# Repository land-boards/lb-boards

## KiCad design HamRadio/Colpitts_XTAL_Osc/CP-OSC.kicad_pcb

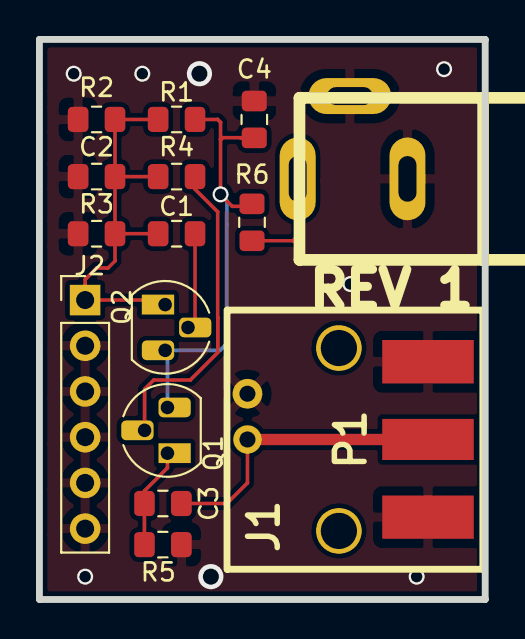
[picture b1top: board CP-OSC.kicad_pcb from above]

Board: 2 copper layers, 24.8 x 31.1 mm, 16 parts (0 on the bottom side), 8 nets.

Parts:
C1, C2: 470PF; C_0805_2012Metric_Pad1.15x1.40mm_HandSolder
C3: 100pF; C_0805_2012Metric_Pad1.15x1.40mm_HandSolder
C4: 0.1uF; C_0805_2012Metric_Pad1.15x1.40mm_HandSolder
J1: BNC; BNC-RT
J2: Conn_01x06; PinHeader_1x06_P2.54mm_Vertical
J3: DCJ0202; DCJ-NEW-Slotted
P1: SMA; SMA_EDGE
Q1, Q2: 2N3904; TO-92_HandSolder
R1, R2: 10K; R_0805_2012Metric_Pad1.15x1.40mm_HandSolder
R3, R4, R5: 1K; R_0805_2012Metric_Pad1.15x1.40mm_HandSolder
R6: 47; R_0805_2012Metric_Pad1.15x1.40mm_HandSolder

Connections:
GND: C2.2, C4.2, J1.2, J2.2, J2.3, J2.4, J2.5, J2.6, J3.2, J3.3, P1.2, R2.1, R3.1, R5.1
unnamed: C1.1, Q1.2
unnamed: C1.2, C2.1, J2.1, Q1.1, R1.1, R2.2, R3.2, R4.2
unnamed: C3.1, J1.1, P1.1
unnamed: C3.2, Q2.1, R5.2
unnamed: C4.1, Q1.3, Q2.3, R1.2, R6.2
unnamed: J3.1, R6.1
unnamed: Q2.2, R4.1

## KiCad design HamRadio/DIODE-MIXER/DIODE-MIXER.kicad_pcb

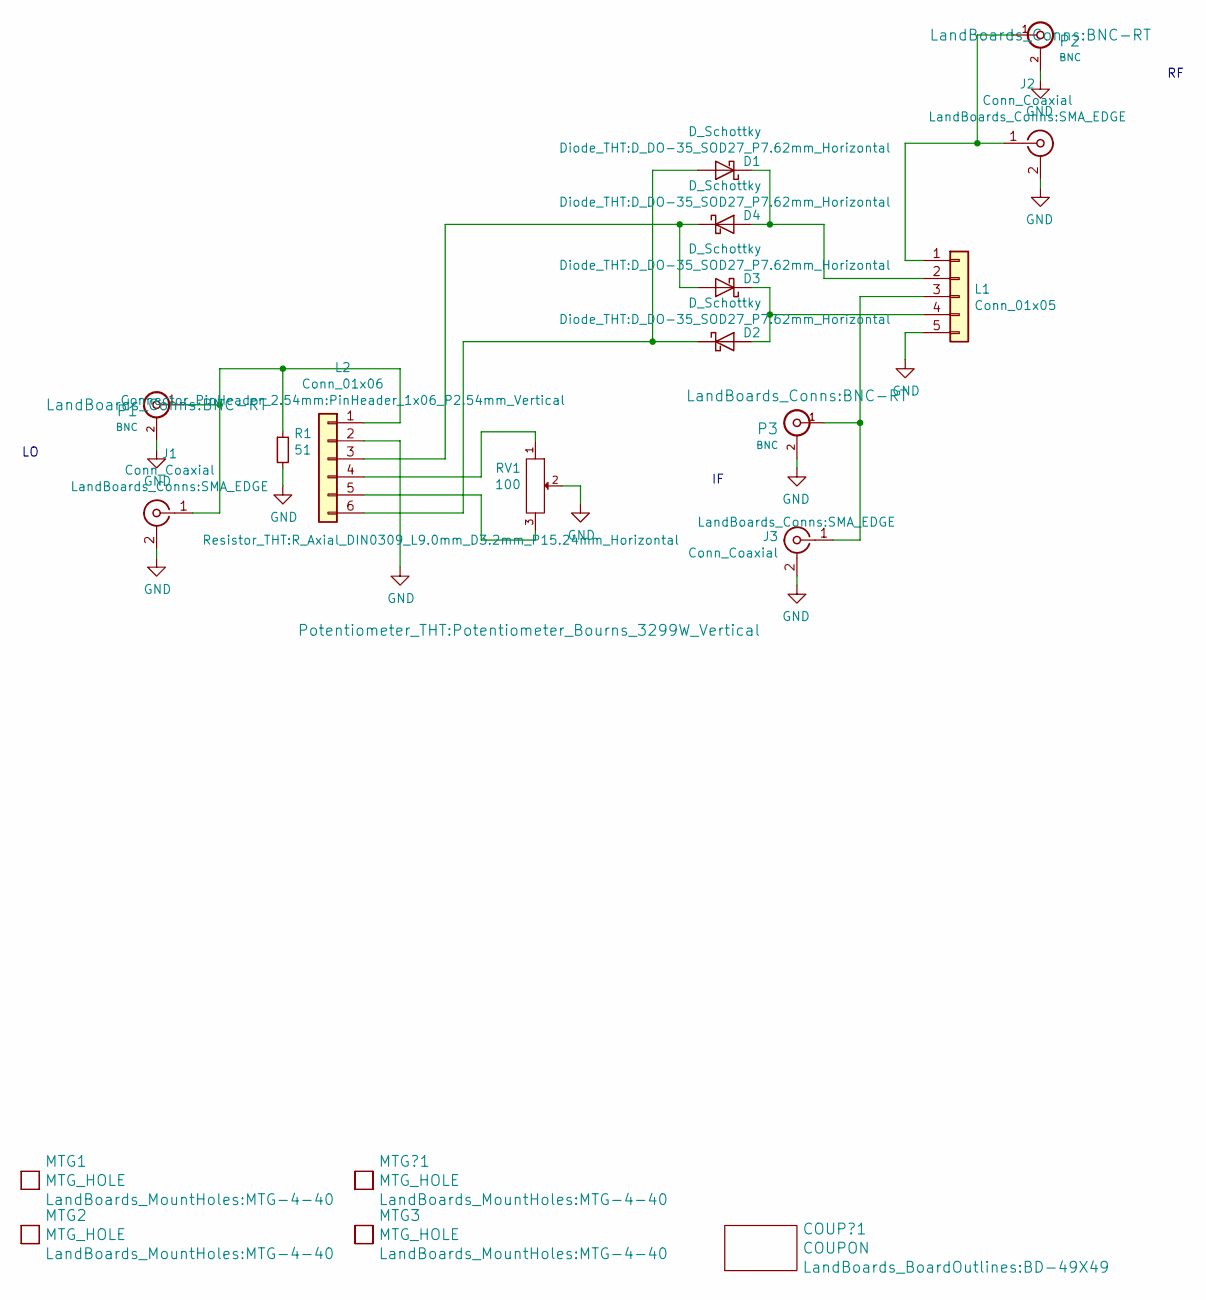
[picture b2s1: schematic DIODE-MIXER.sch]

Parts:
COUP?1: COUPON; BD-49X49
D1, D2, D3, D4: D_Schottky; D_DO-35_SOD27_P7.62mm_Horizontal
J1, J2, J3: Conn_Coaxial; SMA_EDGE
L1: Conn_01x05; PinHeader_1x05_P2.54mm_Vertical
L2: Conn_01x06; PinHeader_1x06_P2.54mm_Vertical
MTG1, MTG2, MTG3: MTG_HOLE; MTG-4-40
MTG?1: MTG_HOLE; MTG-4-40
P1, P2, P3: BNC; BNC-RT
R1: 51; R_Axial_DIN0309_L9.0mm_D3.2mm_P15.24mm_Horizontal
RV1: 100; Potentiometer_Bourns_3299W_Vertical

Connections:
GND: J1.2 (Ext), J2.2 (Ext), J3.2 (Ext), L1.5, L2.2, P1.2 (Ext), P2.2 (Ext), P3.2 (Ext), R1.2, RV1.2
unnamed: D1.1 (K), D4.2 (A), L1.2
unnamed: D1.2 (A), D2.1 (K), L2.6
unnamed: D2.2 (A), D3.1 (K), L1.4
unnamed: D3.2 (A), D4.1 (K), L2.3
unnamed: J1.1 (In), L2.1, P1.1 (In), R1.1
unnamed: J2.1 (In), L1.1, P2.1 (In)
unnamed: J3.1 (In), L1.3, P3.1 (In)
unnamed: L2.4, RV1.1
unnamed: L2.5, RV1.3

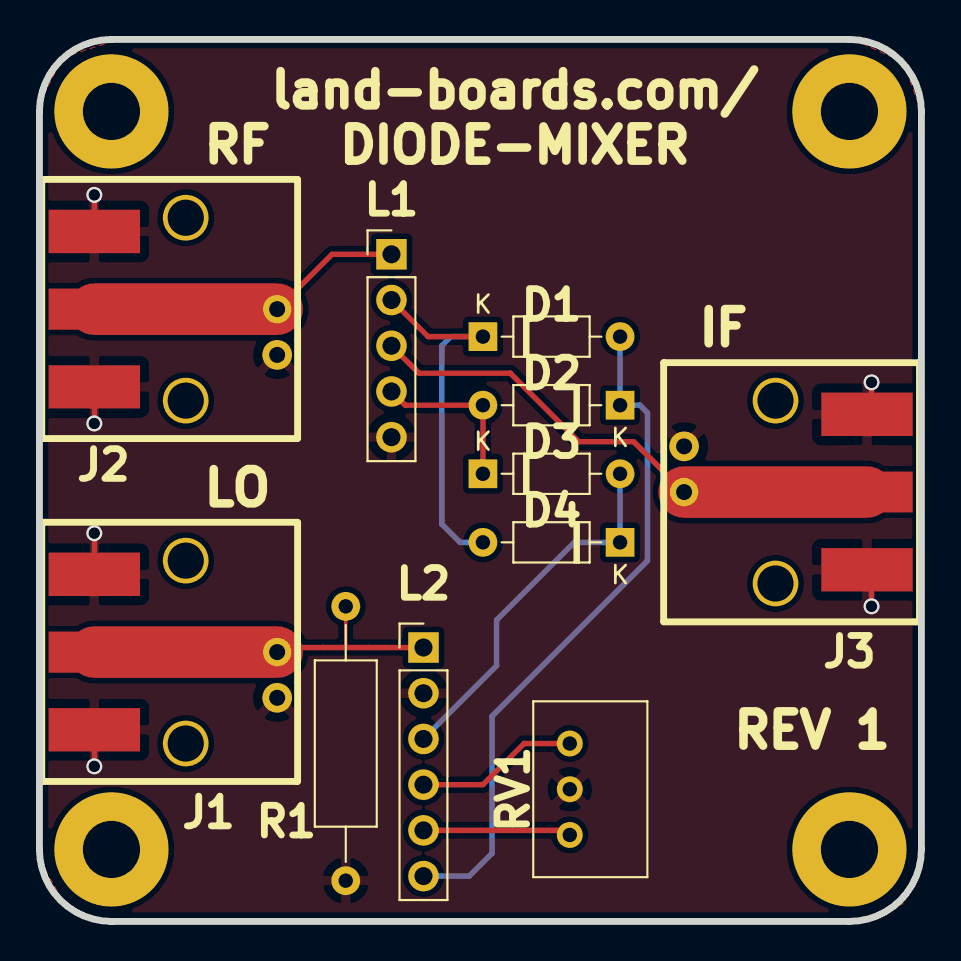
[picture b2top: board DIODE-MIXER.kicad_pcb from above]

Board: 2 copper layers, 49.0 x 49.0 mm, 18 parts (0 on the bottom side), 10 nets.

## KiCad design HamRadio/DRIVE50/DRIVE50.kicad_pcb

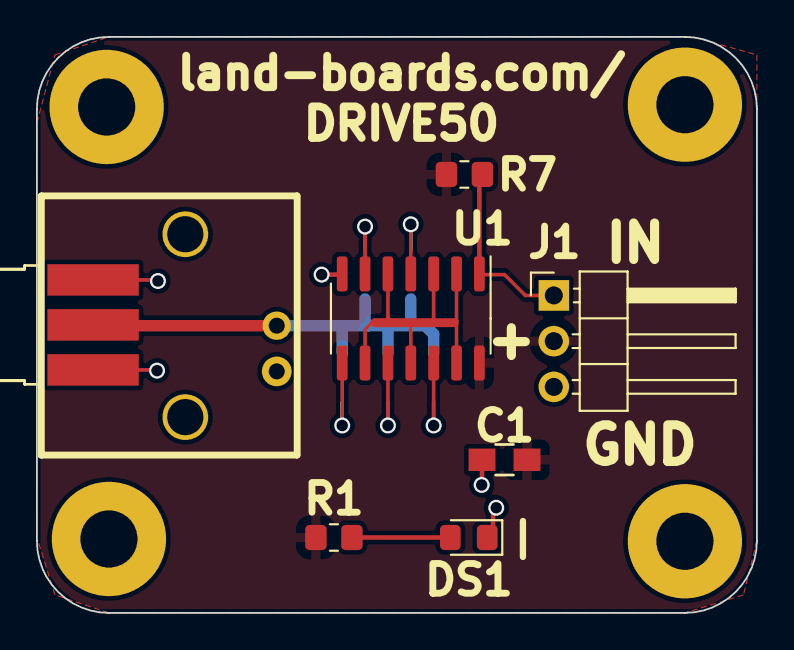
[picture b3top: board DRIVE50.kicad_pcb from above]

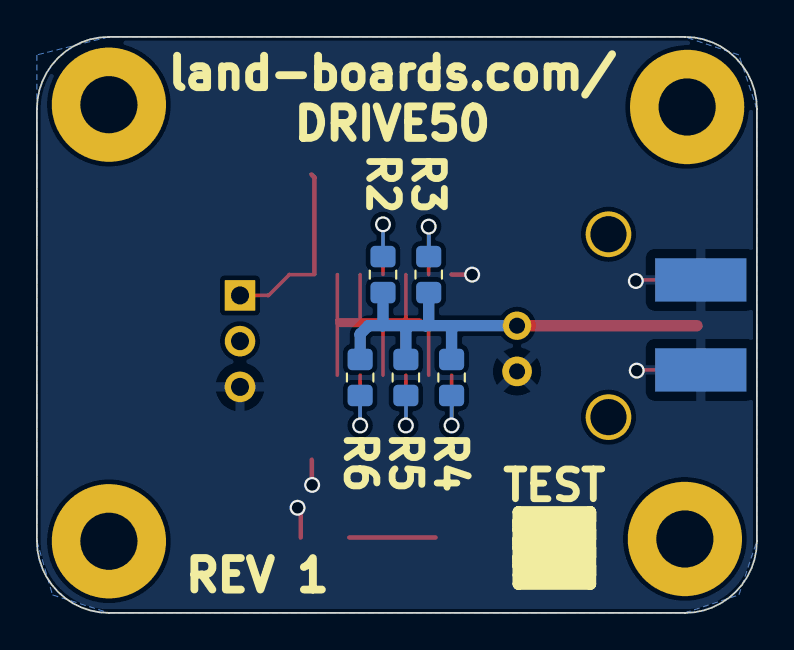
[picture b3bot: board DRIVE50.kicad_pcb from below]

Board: 2 copper layers, 40.0 x 32.0 mm, 18 parts (5 on the bottom side), 11 nets.

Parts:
C1: 0.1uF; C_0805_HandSoldering
DS1: LED; LED_0805_2012Metric_Pad1.15x1.40mm_HandSolder
J1: Conn_01x03; PinHeader_1x03_P2.54mm_Horizontal
MTG1, MTG2, MTG3, MTG4: MTG_HOLE; MTG-4-40
PA1: SMA; SMA_EDGE-F
PB1: BNC; BNC-RT
R1: 240; R_0805_2012Metric_Pad1.20x1.40mm_HandSolder
R2, R3, R4, R5, R6: 249; R_0805_2012Metric_Pad1.20x1.40mm_HandSolder
R7: 10K; R_0805_2012Metric_Pad1.20x1.40mm_HandSolder
TEST: COUPON; TEST_BLK-REAR
U1: 74AC14; SO-14_3.9x8.65mm_P1.27mm

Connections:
GND: C1.2, DS1.1 (K), J1.3, PA1.2 (Ext), PB1.2 (Ext), U1.7 (GND)
unnamed: DS1.2 (A), R1.2
unnamed: J1.1, R7.1, U1.1
unnamed: PA1.1 (In), PB1.1 (In), R2.2, R3.2, R4.2, R5.2, R6.2
unnamed: R2.1, U1.4
unnamed: R3.1, U1.6
unnamed: R4.1, U1.8
unnamed: R5.1, U1.10
unnamed: R6.1, U1.12
unnamed: U1.2, U1.3, U1.5, U1.9, U1.11, U1.13
VCC: C1.1, J1.2, R1.1, R7.2, U1.14 (VCC)

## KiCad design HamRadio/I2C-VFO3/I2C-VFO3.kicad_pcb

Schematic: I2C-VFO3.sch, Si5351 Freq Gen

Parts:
C1, C2: 0.1uF; C_0805_2012Metric_Pad1.15x1.40mm_HandSolder
J1: Conn_02x04_Odd_Even; PinHeader_2x04_P2.54mm_Vertical
J2: Conn_02x03_Odd_Even; PinHeader_2x03_P2.54mm_Vertical
R1, R2: 2.2K; R_0805_2012Metric_Pad1.15x1.40mm_HandSolder
U1: Si5351A; MSOP-10_3x3mm_P0.5mm
U2: ASE-xxxMHz; Oscillator_SMD_EuroQuartz_XO53-4Pin_5.0x3.2mm_HandSoldering

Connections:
+3V3: C1.1, J1.5, J1.6, R1.1, R2.1, U1.1 (VCC), U1.7 (VCCO), U2.4
/SCL: J1.1, J1.2, R1.2, U1.4 (SCL)
/SDA: J1.3, J1.4, R2.2, U1.5 (SDA)
GND: C1.2, J1.7, J1.8, J2.2, J2.4, J2.6, U1.8 (GND), U2.2
unnamed: C2.1, U1.2 (XA)
unnamed: C2.2, U2.3
unnamed: J2.1, U1.10 (CLK0)
unnamed: J2.3, U1.9 (CLK1)
unnamed: J2.5, U1.6 (CLK2)

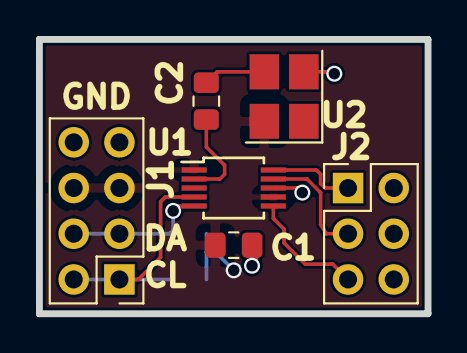
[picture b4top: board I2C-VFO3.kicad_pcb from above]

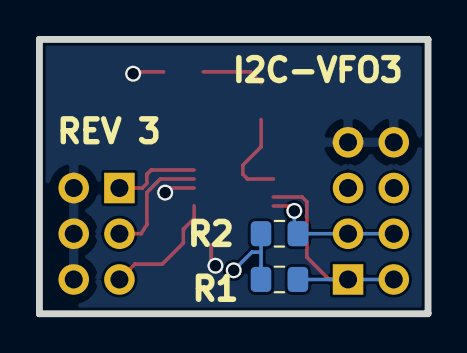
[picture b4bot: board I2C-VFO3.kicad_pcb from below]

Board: 2 copper layers, 21.6 x 15.2 mm, 8 parts (2 on the bottom side), 9 nets.

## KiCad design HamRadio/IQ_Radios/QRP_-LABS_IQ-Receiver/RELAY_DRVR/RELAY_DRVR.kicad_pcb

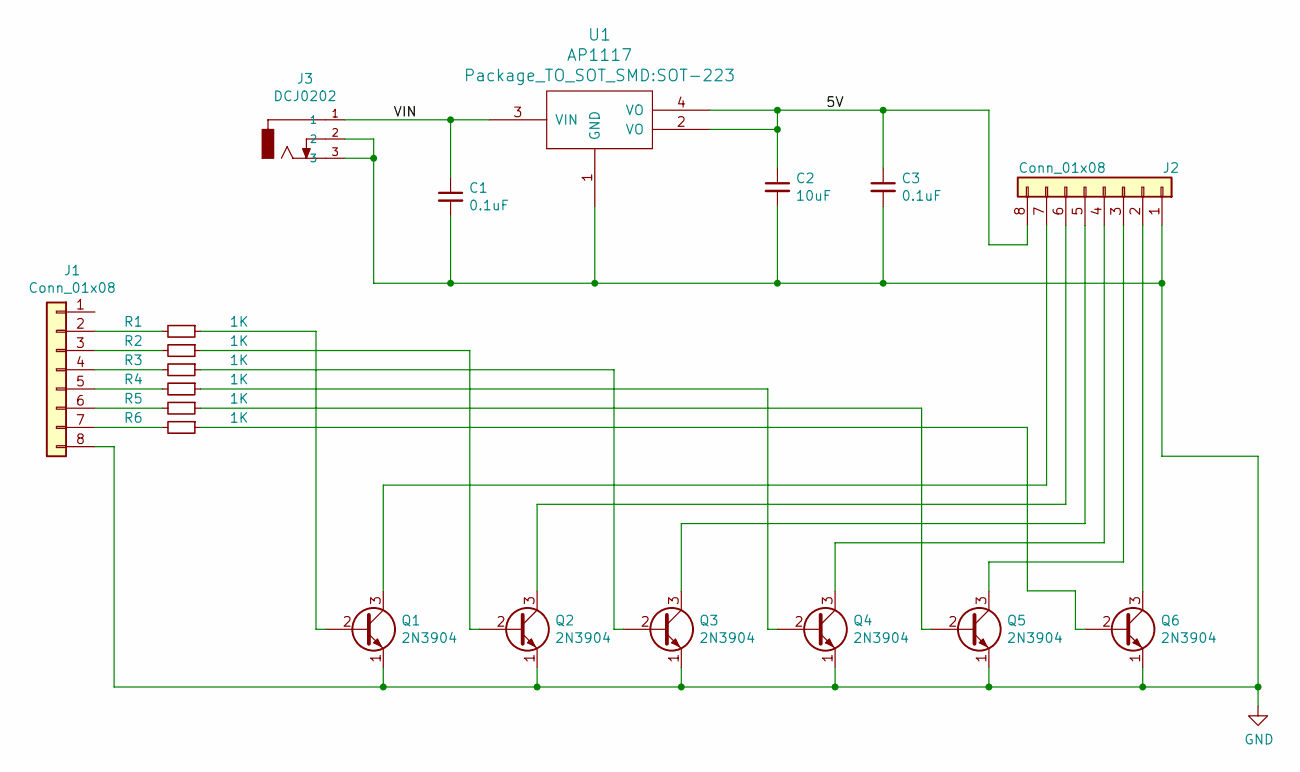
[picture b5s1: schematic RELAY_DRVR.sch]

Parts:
C1, C3: 0.1uF; C_0805_2012Metric_Pad1.18x1.45mm_HandSolder
C2: 10uF; C_1206_3216Metric_Pad1.42x1.75mm_HandSolder
J1, J2: Conn_01x08; PinHeader_1x08_P2.54mm_Horizontal
J3: DCJ0202; DCJ-NEW-Slotted
Q1, Q2, Q3, Q4, Q5, Q6: 2N3904; TO-92_Inline
R1, R2, R3, R4, R5, R6: 1K; R_0805_2012Metric_Pad1.20x1.40mm_HandSolder
U1: AP1117; SOT-223

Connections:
/5V: C2.1, C3.1, J2.8, U1.2 (VO), U1.4 (VO)
/VIN: C1.1, J3.1, U1.3 (VIN)
GND: C1.2, C2.2, C3.2, J1.8, J2.1, J3.2, J3.3, Q1.1 (E), Q2.1 (E), Q3.1 (E), Q4.1 (E), Q5.1 (E), Q6.1 (E), U1.1 (GND)
unnamed: J1.2, R1.2
unnamed: J1.3, R2.2
unnamed: J1.4, R3.2
unnamed: J1.5, R4.2
unnamed: J1.6, R5.2
unnamed: J1.7, R6.2
unnamed: J2.2, Q6.3 (C)
unnamed: J2.3, Q5.3 (C)
unnamed: J2.4, Q4.3 (C)
unnamed: J2.5, Q3.3 (C)
unnamed: J2.6, Q2.3 (C)
unnamed: J2.7, Q1.3 (C)
unnamed: Q1.2 (B), R1.1
unnamed: Q2.2 (B), R2.1
unnamed: Q3.2 (B), R3.1
unnamed: Q4.2 (B), R4.1
unnamed: Q5.2 (B), R5.1
unnamed: Q6.2 (B), R6.1

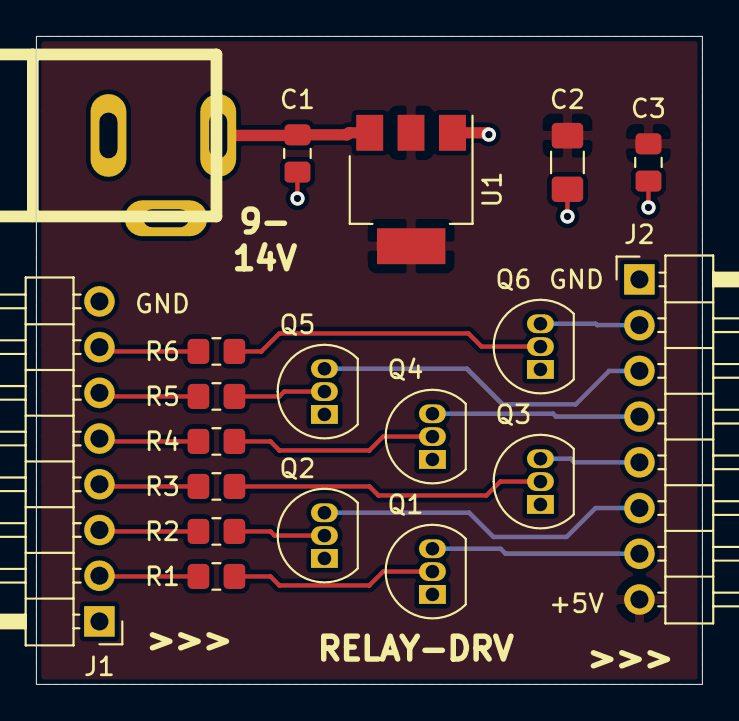
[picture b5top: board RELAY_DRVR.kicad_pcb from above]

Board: 2 copper layers, 37.0 x 36.0 mm, 19 parts (0 on the bottom side), 21 nets.

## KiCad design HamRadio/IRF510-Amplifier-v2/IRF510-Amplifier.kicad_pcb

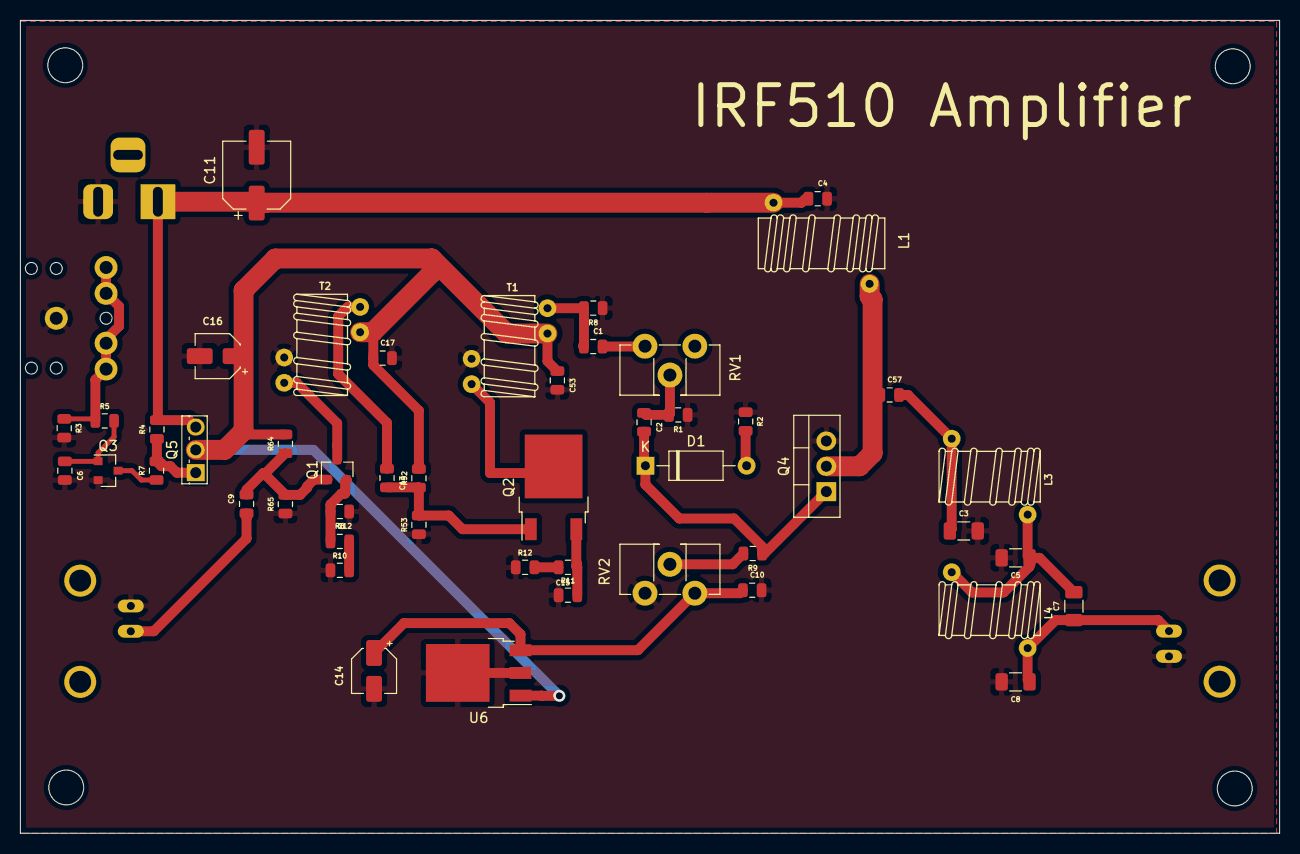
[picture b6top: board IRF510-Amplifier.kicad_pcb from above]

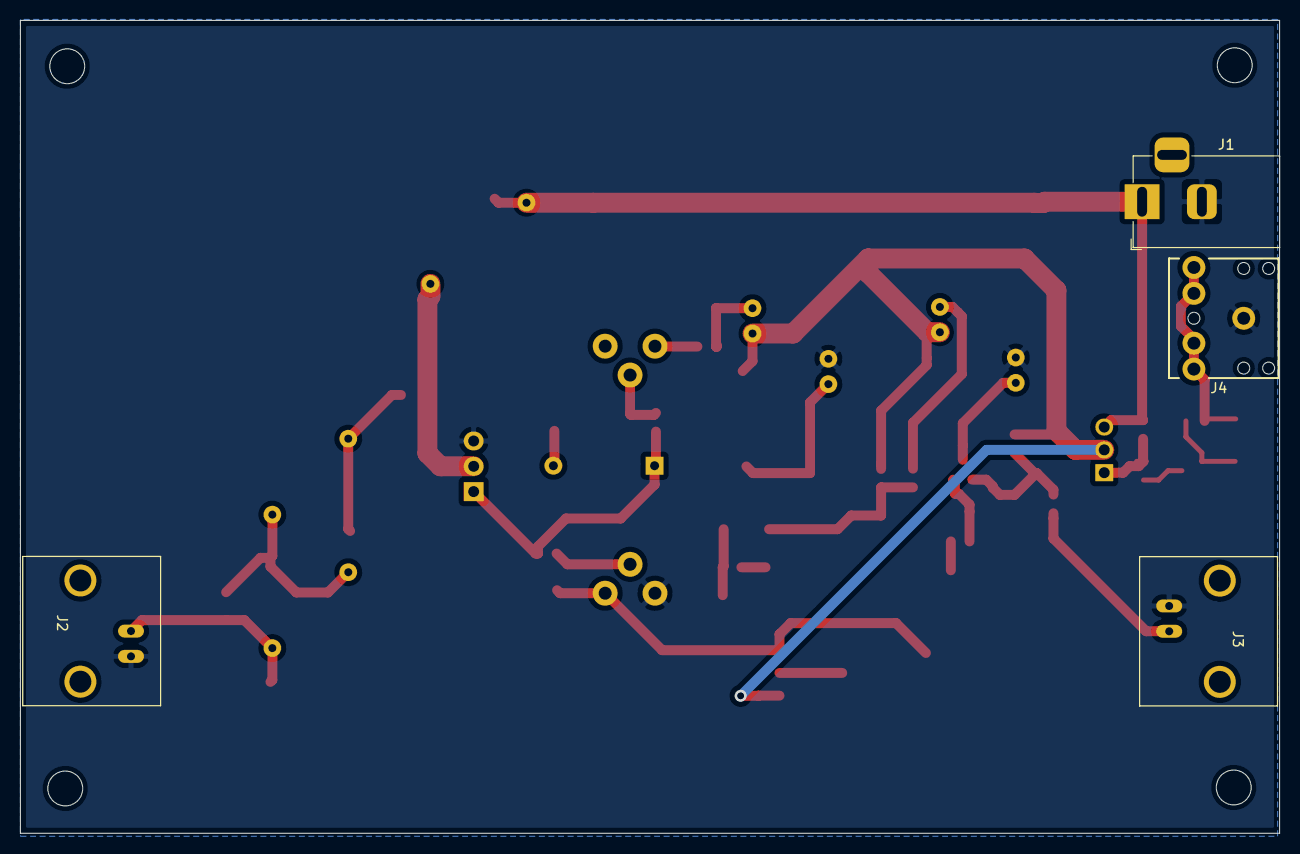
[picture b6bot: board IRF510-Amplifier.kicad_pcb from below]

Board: 2 copper layers, 126.4 x 81.6 mm, 57 parts (4 on the bottom side), 28 nets.

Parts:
 : MountingHole_3.5mm
 #2,  #3,  #4: MountingHole_3.5mm
C1, C2, C4, C6, C9, C10, C12, C13, C15, C17, C53, C57: .1uF; Capacitor 0805
C3, C8: 150p; Capacitor 1206
C5: 330p; Capacitor 1206
C7: 33p; Capacitor 1206
C11: 100uF; Cap_6.3x5.4
C14, C16: 22uF; Cap_4x5.4
D1: D_Zener; D_A-405_P10.16mm_Horizontal
J1: Jack-DC; BarrelJack_Horizontal
J2, J3: BNC
J4: Audio_Jack
L1: T50-43 10T; T50_Inductor
L3: 14T T37-6; T37_Inductor
L4: 18T T37-6; T37_Inductor
Q1: 2N3904-SMD; SOT-23
Q2: 2SC5706; TO-252-2
Q3: BS170F; SOT-23
Q4: IRF510; TO-220-3_Vertical
Q5: IRFU9024; TO-251-3_Vertical
R1: 33; Resistor 0805
R2: 10; Resistor 0805
R3, R4, R7: 10k; Resistor 0805
R5: 1.5k; Resistor 0805
R6, R10: 62; Resistor 0805
R8, R65: 1k; Resistor 0805
R9: 2.7k; Resistor 0805
R11, R12: 18; Resistor 0805
R52: 24k; Resistor 0805
R53: 6.8k; Resistor 0805
R64: 4.7k; Resistor 0805
RV1, RV2: R_POT; Trimpot Vertical
T1: T37-43 8T:4T; T37 Transformer
T2: T37-43 25T:8T; T37 Transformer
U6: MCP1703A-2502_SOT223; TO-252-3_TabPin2

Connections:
12V-On: C16.1, C17.1, C53.1, Q5.2, R52.1, R64.1, T1.C1B, T2.C1B, U6.1
+5V: C10.1, C14.1, RV2.3, U6.3
+12V: C4.1, C11.1, J1.1, L1.1, Q5.3, R4.1
GND: C3.2, C4.2, C5.2, C6.2, C8.2, C10.2, C11.2, C14.2, C16.2, C17.2, C53.2, J1.2, J2.GND, J3.GND, J4.SLEEVE, Q3.2, Q4.3, R1.2, R2.2, R3.1, R6.2, R8.2, R10.2, R11.2, R12.2, R53.2, R65.2, RV2.1, T1.C2A, T2.C2A, U6.2
unnamed: C1.1, R8.1, T1.C2B
unnamed: C1.2, RV1.3
unnamed: C2.1, R1.1, RV1.2
unnamed: C2.2, D1.1, Q4.1, R9.2
unnamed: C3.1, C57.2, L3.1
unnamed: C5.1, C7.2, L3.2, L4.1
unnamed: C6.1, Q3.1, R5.1
unnamed: C7.1, C8.1, J2.S, L4.2
unnamed: C9.1, J3.S
unnamed: C9.2, Q1.1, R64.2, R65.1
unnamed: C12.1, Q1.2, R6.1
unnamed: C12.2, R10.1
unnamed: C13.1, T2.C2B
unnamed: C13.2, Q2.1, R52.2, R53.1
unnamed: C15.1, Q2.3, R11.1
unnamed: C15.2, R12.1
unnamed: C57.1, L1.2, Q4.2
unnamed: D1.2, R2.1
unnamed: J4.RING, J4.RSH, J4.TIP, J4.TSH, R3.2, R5.2
unnamed: Q1.3, T2.C1A
unnamed: Q2.2, T1.C1A
unnamed: Q3.3, R7.2
unnamed: Q5.1, R4.2, R7.1
unnamed: R9.1, RV2.2

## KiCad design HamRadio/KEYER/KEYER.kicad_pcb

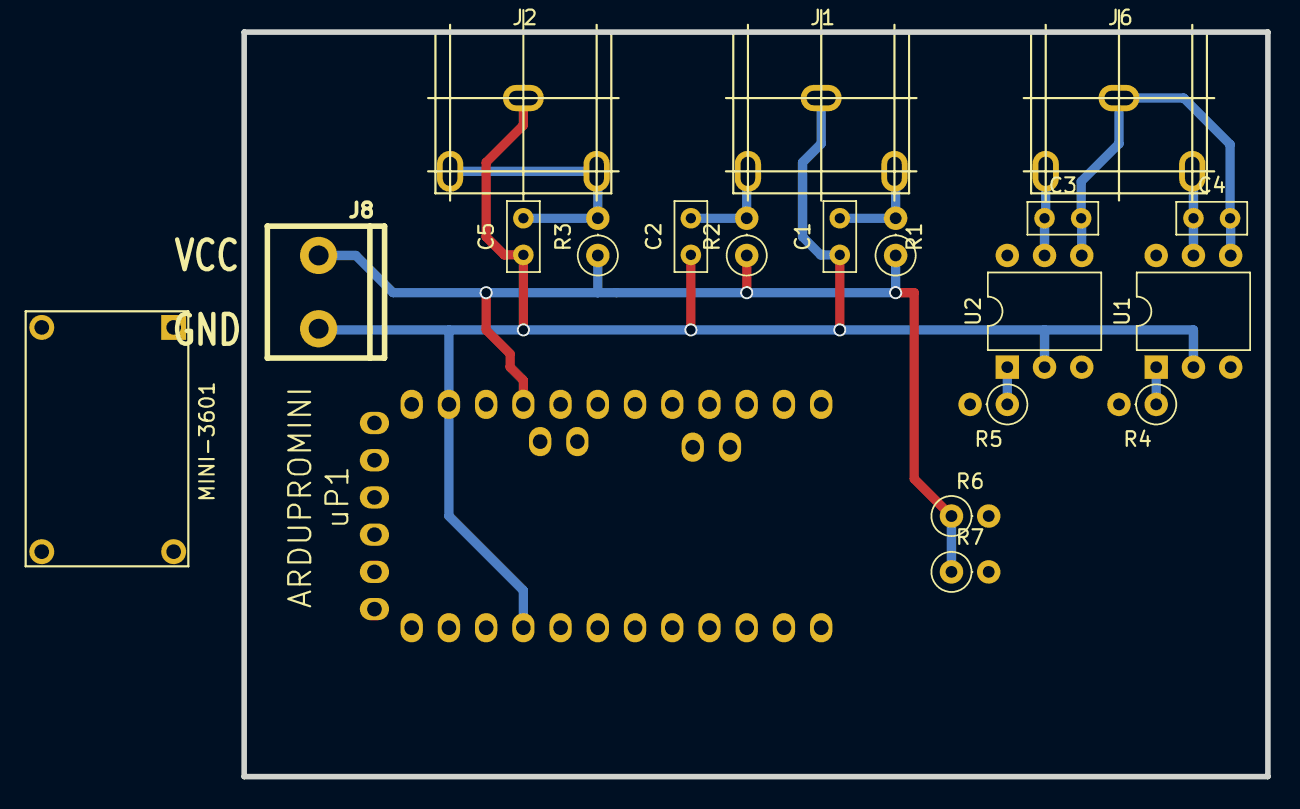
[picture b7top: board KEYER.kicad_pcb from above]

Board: 2 copper layers, 69.8 x 50.8 mm, 20 parts (0 on the bottom side), 14 nets.

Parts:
C1, C2, C3, C4, C5: 0.01uF; C_Rect_L4.6mm_W2.0mm_P2.50mm_MKS02_FKP02
J1, J2, J6: AudioJack3; Jack_3.5mm_CUI_SJ1-352XN_Horizontal
J8: Conn_01x02; TB2-5MM
MINI-3601: MINI-360
R1, R2, R3, R6, R7: 10K; R_Axial_DIN0207_L6.3mm_D2.5mm_P2.54mm_Vertical
R4, R5: 120; R_Axial_DIN0207_L6.3mm_D2.5mm_P2.54mm_Vertical
U1, U2: 4N25; DIP-6_W7.62mm
uP1: ARDUPROMINI; ArduProMini

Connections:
+3V3: J8.1, R1.1, R2.1, R3.1, R6.1, R7.1, uP1.22
/LEFT: C1.1, J1.R, R1.2, uP1.11
/RIGHT: C2.1, J1.T, R2.2, uP1.14
/ROT_A: R6.2, uP1.28
/ROT_B: R7.2, uP1.18
/ST_KEY: C5.1, J2.R, J2.T, R3.2, uP1.12
GND: C1.2, C2.2, C5.2, J1.S, J2.S, J8.2, MINI-3601.OUT-, U1.2, U2.2, uP1.10, uP1.20
unnamed: C3.1, J6.T, U2.5
unnamed: C3.2, C4.2, J6.S, U1.4, U2.4
unnamed: C4.1, J6.R, U1.5
unnamed: R4.1, U1.1
unnamed: R4.2, uP1.30
unnamed: R5.1, U2.1
unnamed: R5.2, uP1.29

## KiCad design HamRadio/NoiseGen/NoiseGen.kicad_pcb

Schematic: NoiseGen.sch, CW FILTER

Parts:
C1, C5: 81PF; C_Rect_L4.0mm_W2.5mm_P2.50mm; MfgPN 1C10Z5U104M050B
C2, C3, C4: 0.01uF; C_Rect_L4.0mm_W2.5mm_P2.50mm; MfgPN 1C10Z5U104M050B
DZ1, DZ2: 5V; D_DO-34_SOD68_P7.62mm_Horizontal
MTG4: MTG_HOLE; MTG-4-40
Q1, Q2: 2N3904; TO-92_HandSolder
R1, R3, R5, R6: 680; R_Axial_DIN0207_L6.3mm_D2.5mm_P10.16mm_Horizontal
R2: 100; R_Axial_DIN0207_L6.3mm_D2.5mm_P10.16mm_Horizontal
R4: 510; R_Axial_DIN0207_L6.3mm_D2.5mm_P10.16mm_Horizontal
R7: 51; R_Axial_DIN0207_L6.3mm_D2.5mm_P10.16mm_Horizontal
TESTED1: COUPON; TEST_BLK-REAR
TP1, TP2, TP3, TP4: TestPoint; TestPoint_THTPad_2.0x2.0mm_Drill1.0mm

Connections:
/+12V: C5.1, R1.2, R3.2, R5.2, R6.2, TP2.1
/N1: C1.1, DZ1.2 (K), R1.1, R2.2, R3.1
/N2: DZ1.1 (A), Q1.2 (B)
/N3: C2.2, Q1.3 (C), R2.1
/N4: C2.1, Q2.2 (B), R4.1
/N5: C4.2, Q2.3 (C), R7.1
/N6: C3.2, DZ2.2 (K), R5.1, R6.1, R7.2
GND: C1.2, C3.1, C5.2, Q1.1 (E), Q2.1 (E), TP3.1, TP4.1
unnamed: C4.1, TP1.1
unnamed: DZ2.1 (A), R4.2

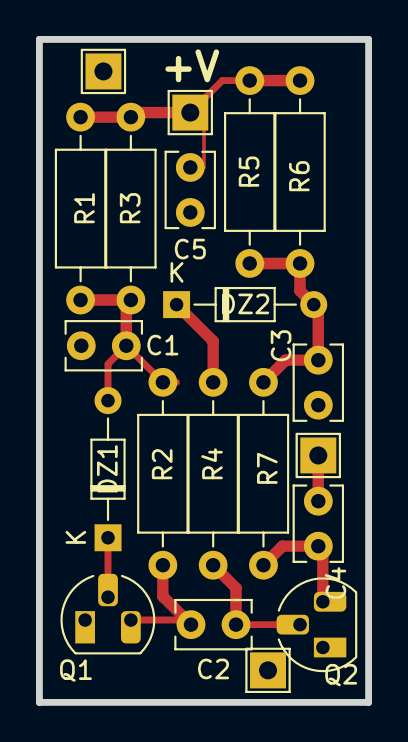
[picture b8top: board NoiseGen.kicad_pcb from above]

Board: 2 copper layers, 18.3 x 36.8 mm, 20 parts (0 on the bottom side), 10 nets.
